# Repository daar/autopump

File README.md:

Autopump is a small project to create an Arduino powered automatic compressed air controller. The controller has an LCD screen and two button interface. Two automatic valves and a pressure transmitter make it possible to achieve accurate control on the target pressure. The original purpose to build such a controller was to make it possible to automatically pump soccer balls, although the controller of course can be used for any purpose.

Below is a rendering of the Arduino UNO shield that is needed to control autopump. The shield connects all peripherals to the Arduino board.

All sourcecode is released under GPL2 license and the hardware is released under the OSHW.

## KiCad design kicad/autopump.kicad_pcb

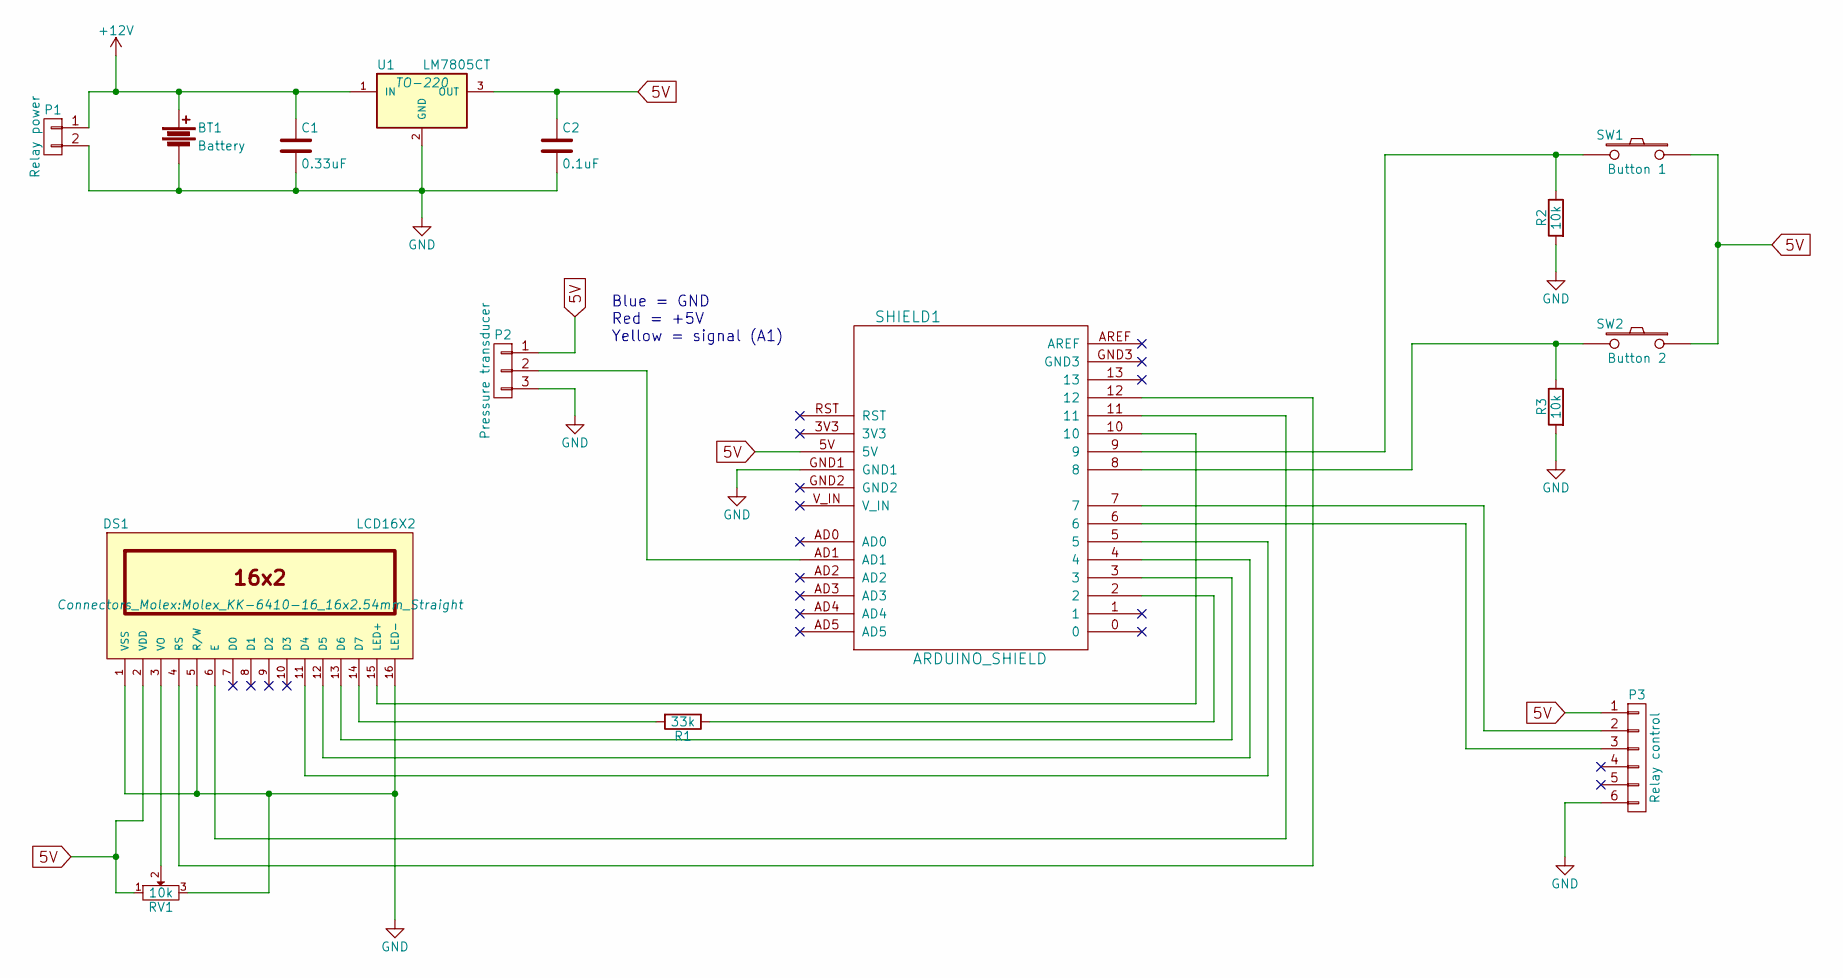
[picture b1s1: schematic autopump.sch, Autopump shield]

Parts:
BT1: Battery; PINHEAD1-2
C1: 0.33uF; C_Radial_D8_L11.5_P3.5
C2: 0.1uF; C_Radial_D8_L11.5_P3.5
DS1: LCD16X2; Molex_KK-6410-16_16x2.54mm_Straight
P1: Relay power; PINHEAD1-2
P2: Pressure transducer; Socket_Strip_Straight_1x03
P3: Relay control; PINHEAD1-6
R1: 33k; Resistor_Horizontal_RM10mm
R2, R3: 10k; Resistor_Horizontal_RM10mm
RV1: 10k; Potentiometer_Trimmer-Piher_PT15-V12-5_horizontal
SHIELD1: ARDUINO_SHIELD; ARDUINO SHIELD
SW1: Button 1; PINHEAD1-2
SW2: Button 2; PINHEAD1-2
U1: LM7805CT; TO-220

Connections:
5V: C2.1, DS1.2 (VDD), P2.1, P3.1, RV1.1, SHIELD1.5V, SW1.1, SW2.1, U1.3 (OUT)
+12V: BT1.1, C1.1, P1.1, U1.1 (IN)
GND: BT1.2, C1.2, C2.2, DS1.1 (VSS), DS1.5 (R/W), DS1.16 (LED-), P1.2, P2.3, P3.6, R2.2, R3.2, RV1.3, SHIELD1.GND1, U1.2 (GND)
unnamed: DS1.3 (VO), RV1.2
unnamed: DS1.4 (RS), SHIELD1.12
unnamed: DS1.6 (E), SHIELD1.11
unnamed: DS1.11 (D4), SHIELD1.5
unnamed: DS1.12 (D5), SHIELD1.4
unnamed: DS1.13 (D6), SHIELD1.3
unnamed: DS1.14 (D7), R1.2
unnamed: DS1.15 (LED+), SHIELD1.10
unnamed: P2.2, SHIELD1.AD1
unnamed: P3.2, SHIELD1.7
unnamed: P3.3, SHIELD1.6
unnamed: R1.1, SHIELD1.2
unnamed: R2.1, SHIELD1.9, SW1.2
unnamed: R3.1, SHIELD1.8, SW2.2

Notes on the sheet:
Blue = GND Red = +5V Yellow = signal (A1)

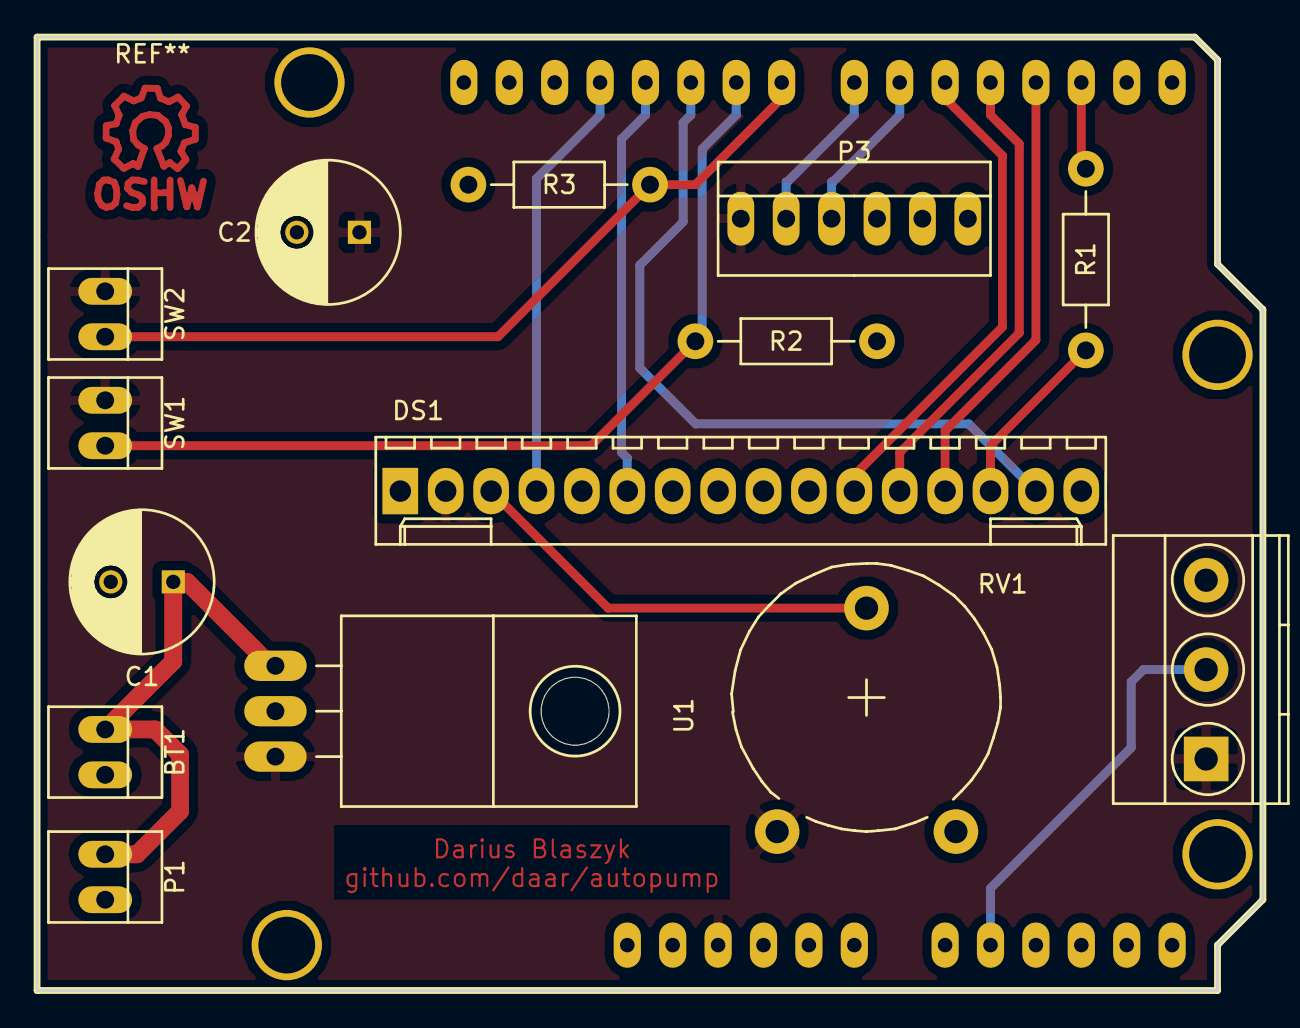
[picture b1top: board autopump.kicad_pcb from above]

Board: 2 copper layers, 68.6 x 53.3 mm, 15 parts (0 on the bottom side), 17 nets.

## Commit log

2015-09-13 Initial commit. Added TFT libraries from ADA fruit and a main files that displays basic information
2016-07-16 More work on the autopump source code. The basic code is now implemented. Please note that TFT screen support has been droped in favor of LCD screen support. A start has been made with creating a fri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
2016-07-17 autopump - added one more preset - reorganized some variables and code - turn of LCD display in step 0 - automatic formatting of source code - added automatic reset time to steps 1 and 2 - renamed ti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
    parts
    - added pictures and description of some of the parts used
2016-07-20 fixed quite some issues while debugging; - damping LCD screen output - fixing output (first line) - fixed changing steps form 1 -> 2 - added some more debugging to serial monitor - and some more
2016-07-21 run the deflate and inflate cycles two times consecutively for optimal results display update is controlled in printdisplay() changed order of presets from small to large
2016-07-21 define calculations are written out full, somehow this did not work properly giving false results pressure tolerance from 0.05bar to 0.01bar (just a guess now) increased the preselect values a little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
2016-07-25 Removed the fritzing files. Unfortunatly fritizing does not seem to be stable here. Initial work using kicad. Please note that the work is far from ready. Need to add a few items like: - transistor t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
2016-07-25 removed TFT libraries from src folder added GPL2 license header to autopump source code
2016-07-25 moved autopump.ino file to src folder
2016-07-27 More work on the PCB. - make use of the and Arduino shield (http://www.thingiverse.com/thing:9630) library. - reorganize layouts of components - changed the track width and clearances a bit wider - a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
2016-07-28 More work on the schema and PCB - fixed and reorganized the power supply in the schema - changed the footprints to be more suitable - reorgnized the footprints slightly on the PCB for better layout a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
2016-08-02 Removed some unneeded kicad files from github Replaced LM7805 component by the LM7805CT component Added +12V symbol to schema so the PCB design rules work again. Issue #4 Reorganized the board a bit 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
2016-08-02 initial import of documentation for this project import of design files, which are also used in the documentation
2016-08-02 Added images to the documentation Added some more text to the documentation topics hardware and controller Renamed arduino_uno.rst to controller.rst
2016-08-03 doc - added quite some more documentation (self explanatory) - added some images to illustrate the documentation kicad - moved the text a bit on the PCB for better alignment between the components de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
2016-08-03 removed parts folder, this has become part of the documentation
2016-08-03 src - pressure input pin is now a define - be a bit more verbose and print zeropressure to serial - add a delay of 1000ms entering step 2 - renamed the src folder to arduino as the Arduino IDE needs 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
